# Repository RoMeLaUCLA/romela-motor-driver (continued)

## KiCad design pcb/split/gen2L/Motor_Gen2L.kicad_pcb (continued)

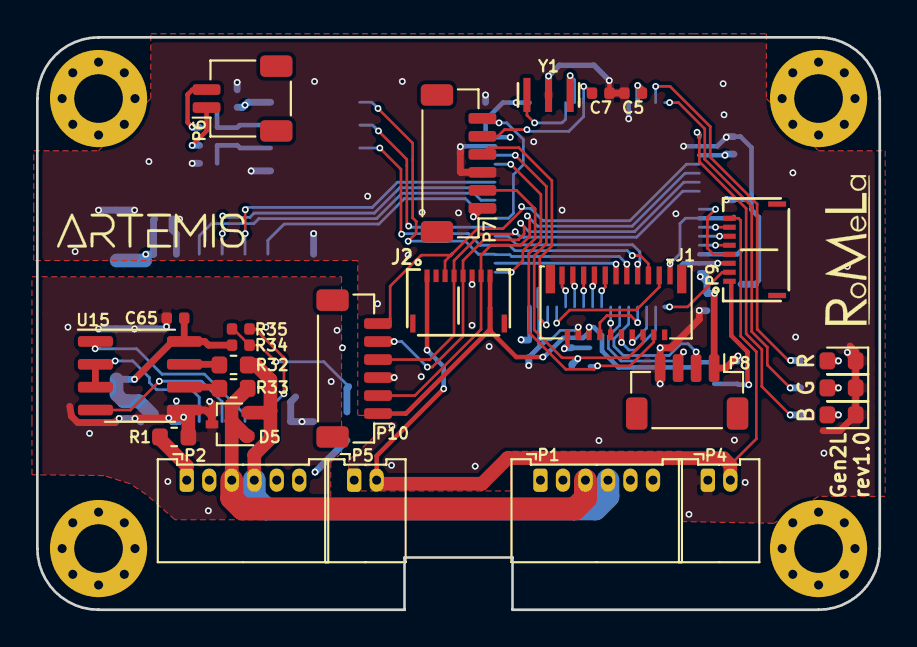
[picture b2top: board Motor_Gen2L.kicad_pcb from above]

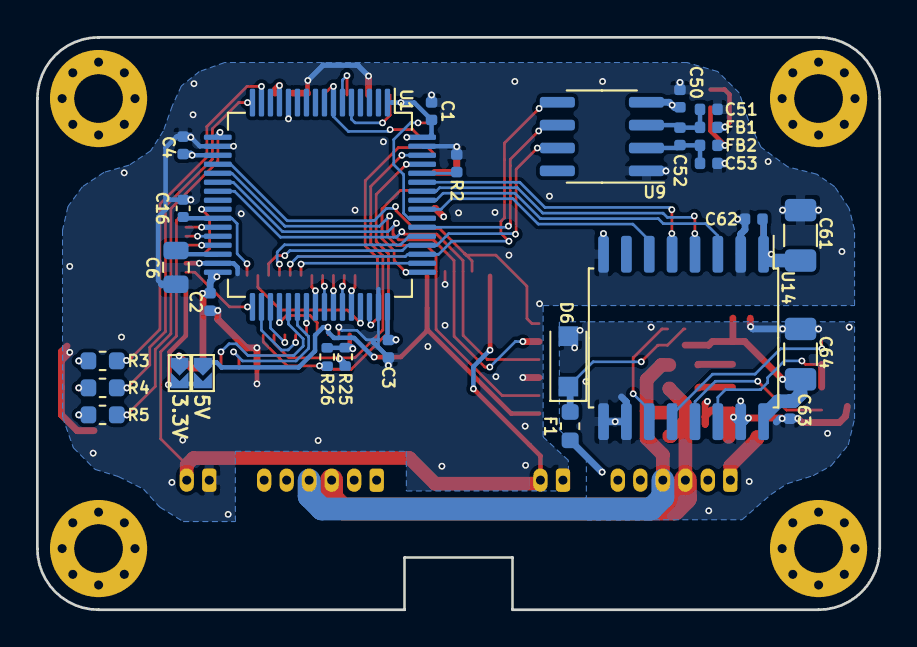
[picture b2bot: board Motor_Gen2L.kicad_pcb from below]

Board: 4 copper layers, 46.8 x 31.8 mm, 60 parts (29 on the bottom side), 71 nets.

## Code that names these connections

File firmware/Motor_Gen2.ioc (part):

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Mcu.Name=STM32F446R(C-E)Tx
Mcu.Package=LQFP64
Mcu.UserName=STM32F446RETx
PA1.Signal=S_TIM5_CH2
PA10.GPIOParameters=GPIO_Speed
PA10.GPIO_Speed=GPIO_SPEED_FREQ_HIGH
PA10.Signal=S_TIM1_CH3
PA11.GPIOParameters=GPIO_Label
PA11.GPIO_Label=ENGATE
PA11.Signal=GPIO_Output
PA12.GPIOParameters=GPIO_PuPd,GPIO_Label
PA12.GPIO_Label=Fault
PA12.GPIO_PuPd=GPIO_PULLUP
PA12.Signal=GPIO_Input
PA13.Mode=Trace_Asynchronous_SW
PA13.Signal=SYS_JTMS-SWDIO
PA14.Mode=Trace_Asynchronous_SW
PA14.Signal=SYS_JTCK-SWCLK
PA15.GPIOParameters=GPIO_Speed,PinState,GPIO_Label
PA15.GPIO_Label=SPI3_NSS_DRV
PA15.GPIO_Speed=GPIO_SPEED_FREQ_VERY_HIGH
PA15.PinState=GPIO_PIN_SET
PA15.Signal=GPIO_Output
PA2.Signal=S_TIM5_CH3
PA3.Signal=S_TIM5_CH4
PA4.GPIOParameters=GPIO_Speed,PinState,GPIO_Label
PA4.GPIO_Label=SPI1_NSS_ENC
PA4.GPIO_Speed=GPIO_SPEED_FREQ_VERY_HIGH
PA4.PinState=GPIO_PIN_SET
PA4.Signal=GPIO_Output
PA5.Mode=Full_Duplex_Master
PA5.Signal=SPI1_SCK
PA6.Mode=Full_Duplex_Master
PA6.Signal=SPI1_MISO
PA7.Mode=Full_Duplex_Master
PA7.Signal=SPI1_MOSI
PA8.GPIOParameters=GPIO_Speed
PA8.GPIO_Speed=GPIO_SPEED_FREQ_HIGH
PA8.Signal=S_TIM1_CH1
PA9.GPIOParameters=GPIO_Speed
PA9.GPIO_Speed=GPIO_SPEED_FREQ_HIGH
PA9.Signal=S_TIM1_CH2
PB0.GPIOParameters=GPIO_Label
PB0.GPIO_Label=ADC1_8_Pv
PB0.Signal=ADCx_IN8
PB1.GPIOParameters=GPIO_Label
PB1.GPIO_Label=ENC_PRESET
PB1.Signal=GPIO_Output
PB10.Mode=Synchronous
PB10.Signal=USART3_TX
PB12.GPIOParameters=GPIO_PuPd
PB12.GPIO_PuPd=GPIO_NOPULL
PB12.Mode=Synchronous
PB12.Signal=USART3_CK
PB13.GPIOParameters=GPIO_PuPd
PB13.GPIO_PuPd=GPIO_NOPULL
PB13.Mode=Full_Duplex_Master
PB13.Signal=SPI2_SCK
PB14.Mode=Full_Duplex_Master
PB14.Signal=SPI2_MISO
PB15.Mode=Full_Duplex_Master
PB15.Signal=SPI2_MOSI
PB2.GPIOParameters=GPIO_Speed,PinState,GPIO_Label
PB2.GPIO_Label=USART3_CSn
PB2.GPIO_Speed=GPIO_SPEED_FREQ_VERY_HIGH
PB2.PinState=GPIO_PIN_SET
PB2.Signal=GPIO_Output
PB3.Mode=Trace_Asynchronous_SW
PB3.Signal=SYS_JTDO-SWO
PB4.GPIOParameters=GPIO_PuPd,GPIO_Label
PB4.GPIO_Label=EXT_DI
PB4.GPIO_PuPd=GPIO_PULLUP
PB4.Signal=GPIO_Input
PB5.GPIOParameters=GPIO_Speed,GPIO_Label
PB5.GPIO_Label=TXEN
PB5.GPIO_Speed=GPIO_SPEED_FREQ_VERY_HIGH
PB5.Signal=GPIO_Output
PB6.Mode=Asynchronous
PB6.Signal=USART1_TX
PB7.Mode=Asynchronous
PB7.Signal=USART1_RX
PB8.GPIOParameters=GPIO_Pu
PB8.GPIO_Pu=GPIO_NOPULL
PB8.Mode=I2C
PB8.Signal=I2C1_SCL
PB9.GPIOParameters=GPIO_Pu
PB9.GPIO_Pu=GPIO_NOPULL
PB9.Mode=I2C
PB9.Signal=I2C1_SDA
PC10.Mode=Full_Duplex_Master
PC10.Signal=SPI3_SCK
PC11.GPIOParameters=GPIO_PuPd
PC11.GPIO_PuPd=GPIO_PULLUP
PC11.Mode=Full_Duplex_Master
PC11.Signal=SPI3_MISO
PC12.Mode=Full_Duplex_Master
PC12.Signal=SPI3_MOSI
PC5.Mode=Synchronous
PC5.Signal=USART3_RX
PC6.Mode=Asynchronous
PC6.Signal=USART6_TX
PC7.Mode=Asynchronous
PC7.Signal=USART6_RX
PC8.GPIOParameters=GPIO_Speed,PinState,GPIO_Label
PC8.GPIO_Label=SPI2_NCS
PC8.GPIO_Speed=GPIO_SPEED_FREQ_VERY_HIGH
PC8.PinState=GPIO_PIN_SET
PC8.Signal=GPIO_Output
PC9.GPIOParameters=GPIO_Label
PC9.GPIO_Label=DRV_ENABLE
PC9.Signal=GPIO_Output
PD2.GPIOParameters=GPIO_Speed,PinState,GPIO_Label
PD2.GPIO_Label=SPI3_NSS_TC
PD2.GPIO_Speed=GPIO_SPEED_FREQ_VERY_HIGH
PD2.PinState=GPIO_PIN_SET
PD2.Signal=GPIO_Output
PH0-OSC_IN.Mode=HSE-External-Oscillator
PH0-OSC_IN.Signal=RCC_OSC_IN
PH1-OSC_OUT.Mode=HSE-External-Oscillator
PH1-OSC_OUT.Signal=RCC_OSC_OUT
RCC.HSE_VALUE=8000000
RCC.SYSCLKFreq_VALUE=180000000
RCC.SYSCLKSource=RCC_SYSCLKSOURCE_PLLCLK
board=Motor_rev2

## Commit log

2024-03-25 Initial commit based on archive from 12/6/2022
2024-03-25 Update README.md with change log
2024-03-25 commit as of 7/1/2023 at RoboCup2023.
2024-05-27 Limit joint torque towards joint limits.
2025-09-28 adding pictures for doc
2025-09-29 updated schematics and added split PCB.
2025-09-29 add diagram
